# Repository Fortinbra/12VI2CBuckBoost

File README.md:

# 12VI2CBuckBoost
A 12V input, variable output, programmable BuckBoost Converter

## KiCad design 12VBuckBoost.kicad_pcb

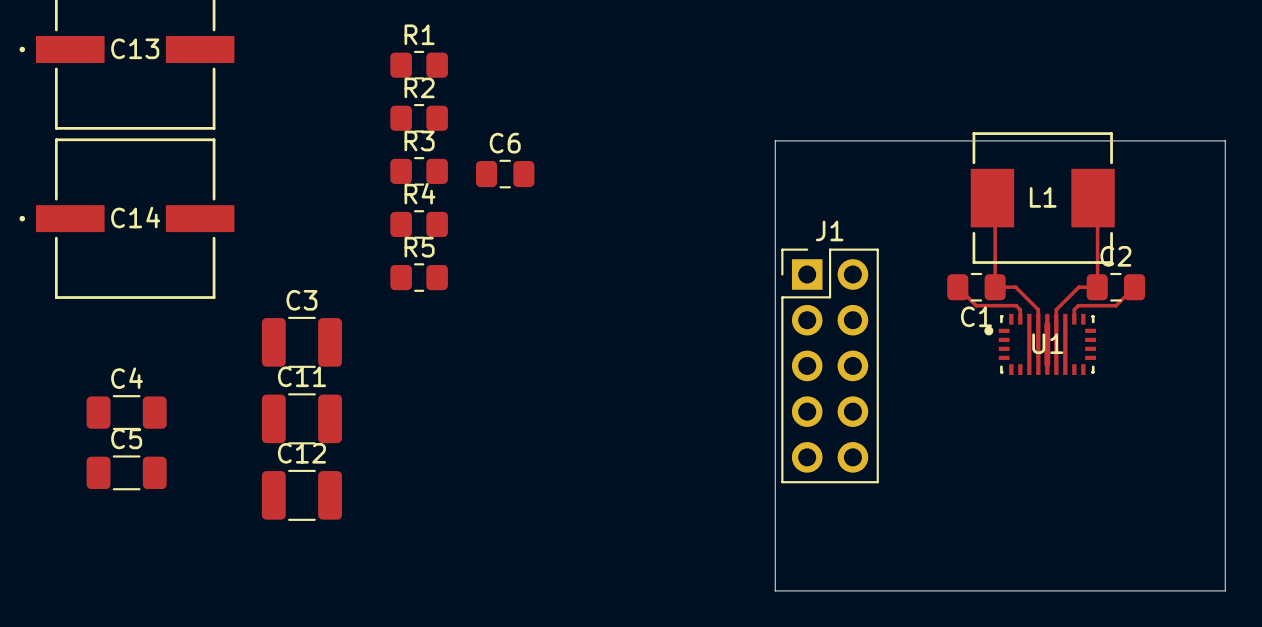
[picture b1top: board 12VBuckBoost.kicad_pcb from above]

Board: 4 copper layers, 25.0 x 25.0 mm, 18 parts (0 on the bottom side), 17 nets.

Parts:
C1, C2: 0.1uF; C_0805_2012Metric_Pad1.18x1.45mm_HandSolder
C3, C12: 22uF X7R; C_1210_3225Metric_Pad1.33x2.70mm_HandSolder
C4, C5: 47uF; C_1206_3216Metric_Pad1.33x1.80mm_HandSolder
C6: 4.7uF; C_0805_2012Metric_Pad1.18x1.45mm_HandSolder
C11: 22uF; C_1210_3225Metric_Pad1.33x2.70mm_HandSolder
C13, C14: 330uF; CAP_ZKU_F_PAN
J1: Conn_02x05_Odd_Even; PinHeader_2x05_P2.54mm_Vertical
L1: 3.3uH; IND_SRP6530A_BRN
R1, R2, R5: 4.7k; R_0805_2012Metric_Pad1.20x1.40mm_HandSolder
R3: 49.9k; R_0805_2012Metric_Pad1.20x1.40mm_HandSolder
R4: 10m; R_0805_2012Metric_Pad1.20x1.40mm_HandSolder
U1: TPS55289RYQR; RYQ0021A-MFG

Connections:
+3.3V: C6.1, J1.8, R1.1, U1.18 (VCC)
+12V: C3.1, C12.1, C13.1, J1.1, J1.2, U1.7 (VIN)
/EN: J1.10, U1.1 (EN_UVLO)
/SCL: J1.7, U1.3 (SCL)
/SDA: J1.9, U1.4 (SDA)
/SW1: C1.1, L1.1, U1.8 (SW1)
/SW2: C2.1, L1.2, U1.10 (SW2)
/VOUT: C4.1, C5.1, C14.1, J1.3, J1.4, R4.1, U1.11 (VOUT), U1.12 (ISP)
GND: C3.2, C4.2, C5.2, C12.2, C13.2, C14.2, J1.5, J1.6, R2.1, U1.9 (PGND)
GNDA: C6.2, C11.2, R3.2, R5.2, U1.17 (AGND)
unnamed: C1.2, U1.20 (BOOT1)
unnamed: C2.2, U1.19 (BOOT2)
unnamed: C11.1, R5.1, U1.15 (COMP)
unnamed: R2.2, U1.21 (EXTVCC)
unnamed: R3.1, U1.6 (FSW)
unnamed: R4.2, U1.13 (ISN)
unnamed: R1.2, U1.2 (MODE)

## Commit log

2025-04-19 Init
